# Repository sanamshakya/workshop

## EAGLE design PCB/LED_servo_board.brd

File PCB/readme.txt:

=====================LED connections

Common anode RGB LED - 1
BC548 - 3
Base Resistor (3K) - 3
LED current limiting resistor - 1

RPi IO pins used for testing - 17, 27, 22 (GPIO-4 has some issue of residual current - LED was not turning off completely. Also sometime LED connected to it does not glow at all.)

======================Servo COntrol

Brown - GND
Red - 5V (>4.8V)
Orange - Signal

Rpi board dimension -

55.56 mm - from circle
center of hole - 46mm horizontal 58mm vertical

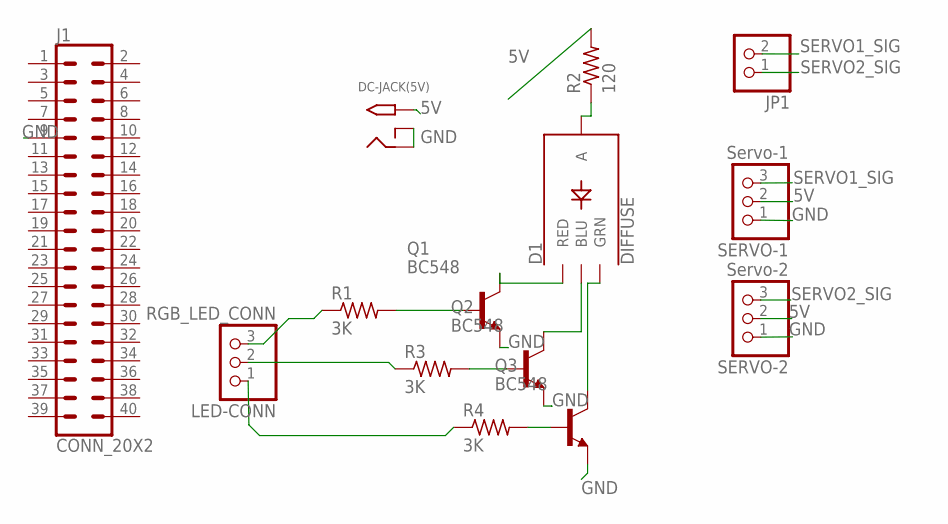
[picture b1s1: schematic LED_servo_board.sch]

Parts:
D1: DIFFUSE; LED-RGB-THRU
DC-JACK(5V): 2.1MMJACKTHM; PJ-102A
J1: CONN_20X2; 2X20
JP1: PINHD-1X2; 1X02
LED-CONN: RGB_LED_CONN; 1X03
Q1, Q2, Q3: BC548; TO92-EBC
R1, R3, R4: 3K; 0204/5
R2: 120; 0204/5
SERVO-1: Servo-1; 1X03
SERVO-2: Servo-2; 1X03

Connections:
5V: DC-JACK(5V).TIP, R2.2, SERVO-1.2, SERVO-2.2
GND: DC-JACK(5V).RING, DC-JACK(5V).RING_SW, J1.9, Q1.E, Q2.E, Q3.E, SERVO-1.1, SERVO-2.1
unnamed: Q1.B, R1.2
unnamed: Q2.B, R3.2
unnamed: Q3.B, R4.2
unnamed: D1.1 (RED), Q1.C
unnamed: D1.4 (BLU), Q2.C
unnamed: D1.3 (GRN), Q3.C
unnamed: D1.2 (A), R2.1
unnamed: LED-CONN.3, R1.1
unnamed: LED-CONN.2, R3.1
unnamed: LED-CONN.1, R4.1
SERVO1_SIG: JP1.2, SERVO-1.3
SERVO2_SIG: JP1.1, SERVO-2.3

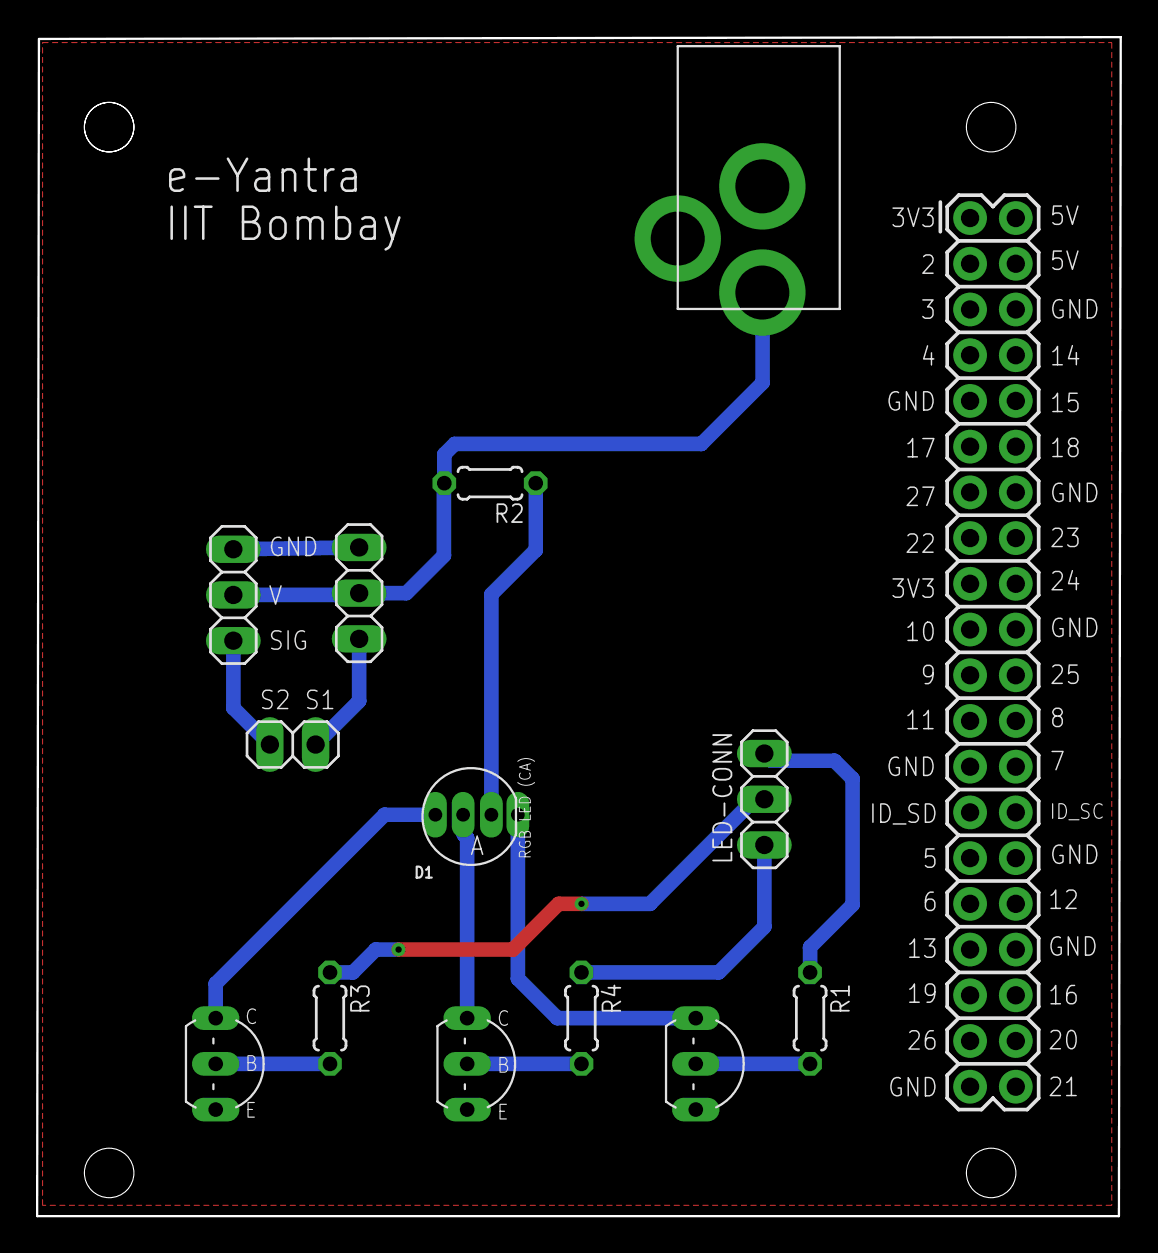
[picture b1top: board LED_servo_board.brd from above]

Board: 2 copper layers, 60.2 x 65.5 mm, 14 parts (0 on the bottom side), 14 nets.

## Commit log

2017-09-16 added topicwise folders
2017-09-16 added the code for image processing first session
2017-09-16 changed the folder structure of ip
2017-09-16 added python code for welcome, LED, servo and PythonLib module
2017-09-17 Added directory to experiment Linux commands
2017-09-17 Added a directory to experiment with Linux Commands
2017-09-17 added the image descriptiona and recognition
2017-09-17 Image Filtering
    Filtering, Morphology and Segmentation
2017-09-17 added the kit test_code
2017-09-17 addding efsi changes
2017-09-18 Added new images
2017-09-18 Added images
2017-09-19 changed to imshow
2017-09-19 added the esc key for closing the window
2017-09-20 added the esc key for exiting the app
2017-09-20 added the images for image description
2018-06-04 Added PCB files

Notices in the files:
parts and their libraries:
SparkFun-Connectors: Licensing: Creative Commons ShareAlike 4.0 International - https://creativecommons.org/licenses/by-sa/4.0
